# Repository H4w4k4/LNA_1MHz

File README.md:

# LNA_1MHz
10Hz to 1MHz Low Noise Amplifier based on Linear Technology AN-159.

<p align="center">

 &nbsp; &nbsp;

</p>

# Design
The design is based on [Linear Technology AN-159 document](https://www.analog.com/en/resources/app-notes/an-159.html#author). It describe how to build a +80dB 10Hz to 1MHz low noise amplifier in order to measure noise level in the 2nV/√Hz range.

Following changes have been done:
+ Design re-routed in KiCad 7.0 to fit nicely into a Hammond 1590BBS housing
+ Selectable +60dB or +80dB gain
+ Full BW output removed

# Measure
A 60dB attenuator is placed on the input of the LNA to measure the frequency response. An Analog Discovery 3 is used as a network analyser.

# Building it
The complete production files are available. The PCB is a 4-layer 102 x 82.6mm and every components is hand solderable. The LNA is powered by 6x AA batteries, consumption is about 100mA. Use the Gerber "housing_Lid_Drill" for drilling the holes in the housing cover. 

Total BOM cost is ~160USD + PCB + shipping.

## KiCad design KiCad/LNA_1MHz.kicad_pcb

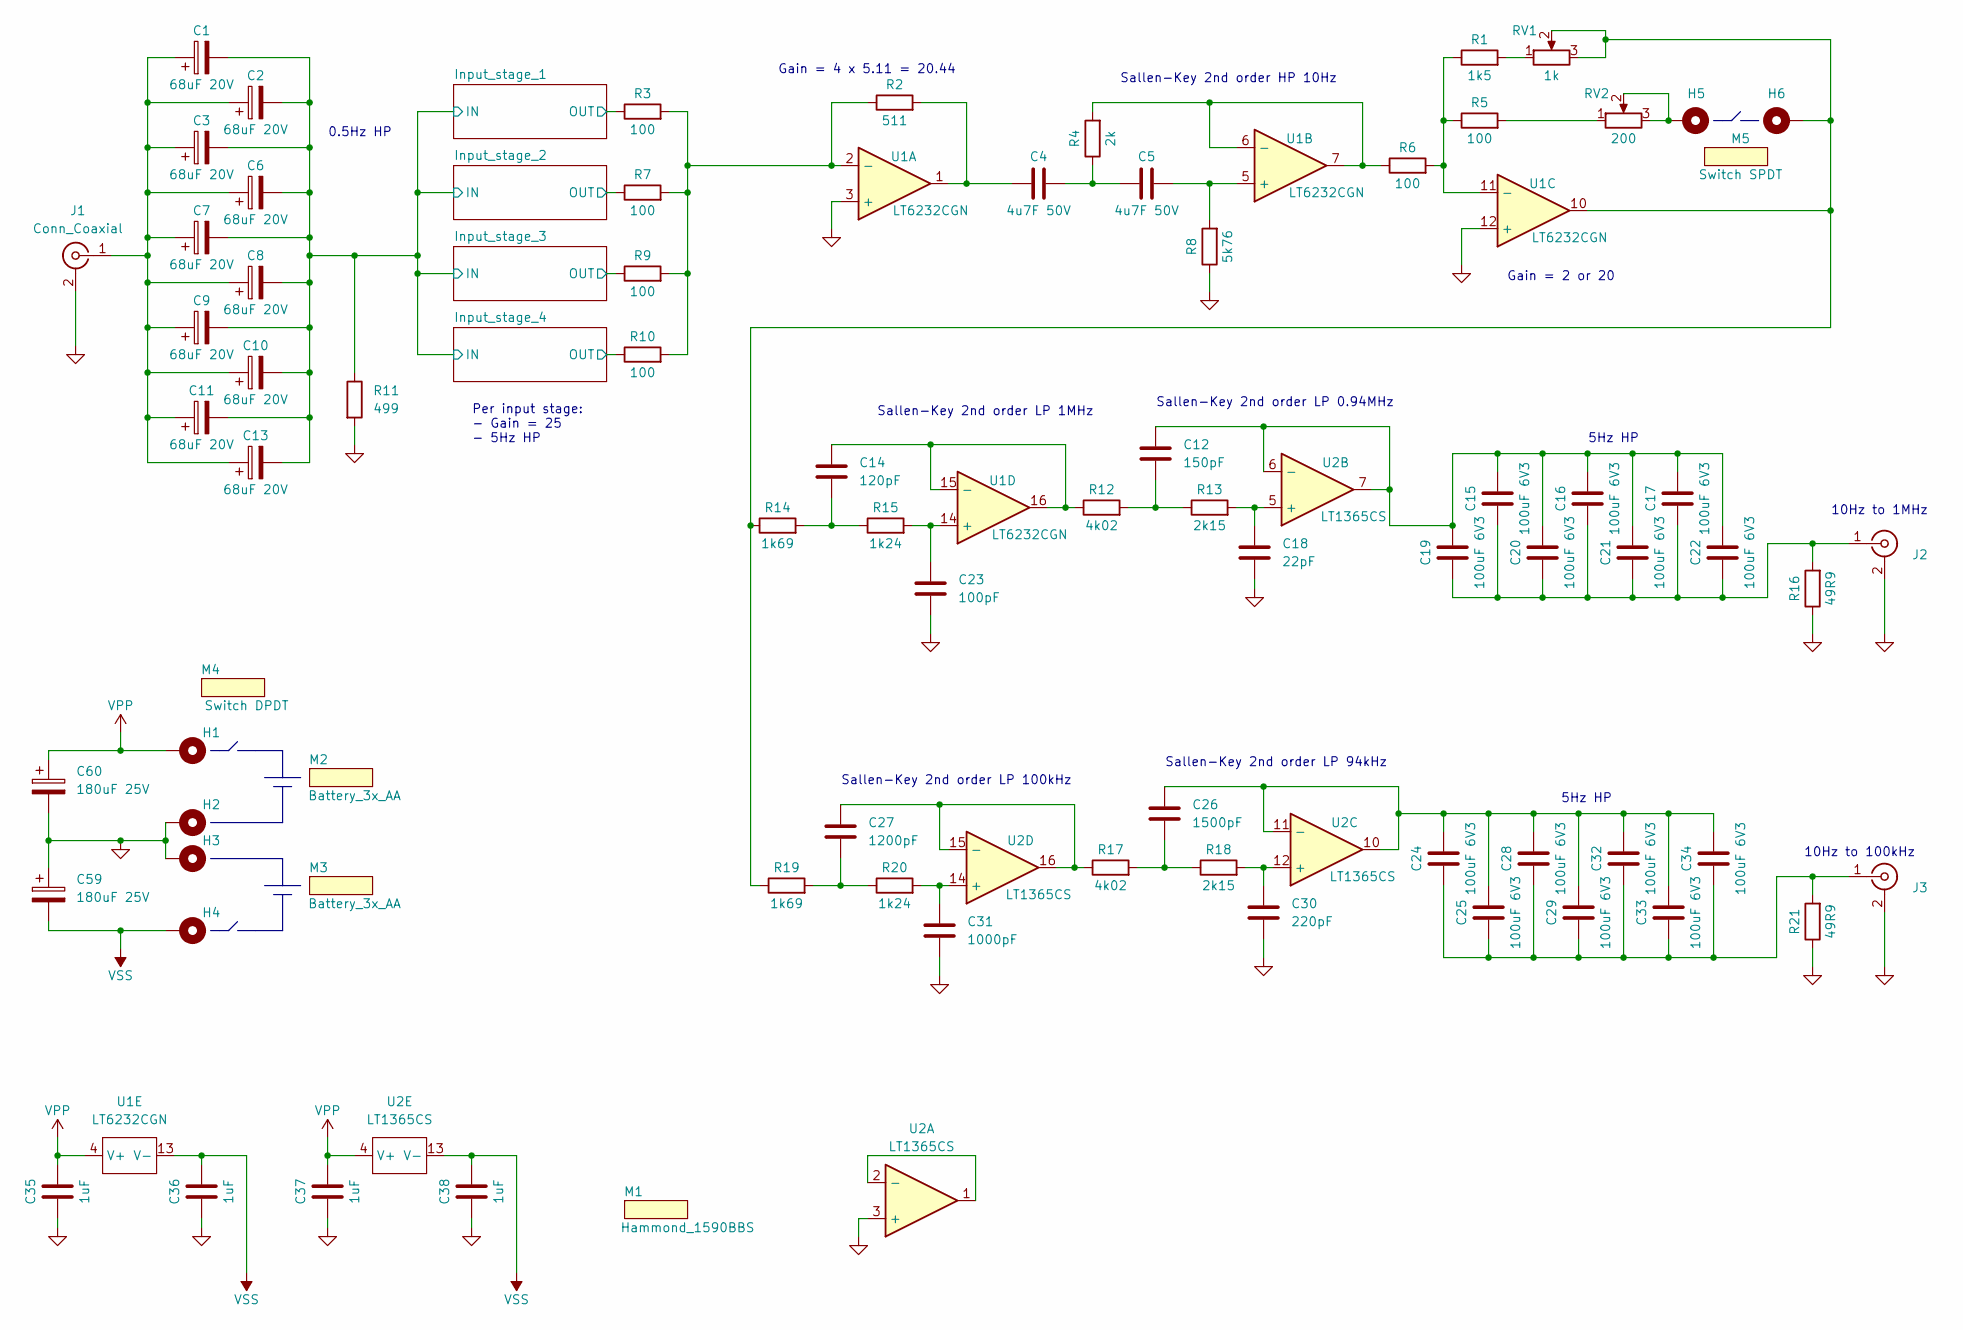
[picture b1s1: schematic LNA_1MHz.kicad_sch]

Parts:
C1, C2, C3, C6, C7, C8, C9, C10, C11, C13: 68uF 20V; CP_EIA-7343-30_AVX-N_Pad2.25x2.55mm_HandSolder; Part AVX, TPSE686M020R0150
C4, C5: 4u7F 50V; C_Rect_L7.2mm_W7.2mm_P5.00mm_FKS2_FKP2_MKS2_MKP2; Part WIMA, MKS2B044701K00K
C12: 150pF; C_1206_3216Metric_Pad1.33x1.80mm_HandSolder; Part AVX, 12065A151JAT2A
C14: 120pF; C_1206_3216Metric_Pad1.33x1.80mm_HandSolder; Part AVX, 12065A121JAT2A
C15, C16, C17, C19, C20, C21, C22, C24, C25, C28, C29, C32, C33, C34: 100uF 6V3; C_1206_3216Metric_Pad1.33x1.80mm_HandSolder; Part MURATA, GRM31CR60J107ME39L
C18: 22pF; C_1206_3216Metric_Pad1.33x1.80mm_HandSolder; Part AVX, 12065A220JAT2A
C23: 100pF; C_1206_3216Metric_Pad1.33x1.80mm_HandSolder; Part AVX, 12065A101JAT2A
C26: 1500pF; C_1206_3216Metric_Pad1.33x1.80mm_HandSolder; Part AVX, 12065A152JAT2A
C27: 1200pF; C_1206_3216Metric_Pad1.33x1.80mm_HandSolder; Part AVX, 12065A122JAT2A
C30: 220pF; C_1206_3216Metric_Pad1.33x1.80mm_HandSolder; Part AVX, 12065A221JAT2A
C31: 1000pF; C_1206_3216Metric_Pad1.33x1.80mm_HandSolder; Part AVX, 12065A102JAT2A
C35, C36, C37, C38: 1uF; C_Rect_L7.2mm_W5.5mm_P5.00mm_FKS2_FKP2_MKS2_MKP2; Part WIMA, MKS2C041001F00K
C59, C60: 180uF 25V; CP_Radial_D8.0mm_P3.50mm; Part PANASONIC, 25SEPF180M
H1, H2, H3, H4, H5, H6: TestPoint_THTPad_2.0x2.0mm_Drill1.0mm
J1: Conn_Coaxial; BNC_TycoElect_5227; Part TE 5227673­1, TE 1­329632­2, TE 1­32963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
J2, J3: Conn_Coaxial; BNC_TycoElect_5227; Part TE 5227222-3, TE 1­329632­2, TE 1­32963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
M1: Hammond_1590BBS; Part Hammond, 1590BBS
M2, M3: Battery_3x_AA; Battery_Holder_3x_AA_no_pin; Part Multicomp, MP000331
M4: Switch DPDT; Multicomp, 1MD1T1B5M1QE; Part Multicomp, 1MD1T1B5M1QE
M5: Switch SPDT; Multicomp, 1MS1T1B5M1QE; Part Multicomp, 1MS1T1B5M1QE
R1: 1k5; R_1206_3216Metric_Pad1.30x1.75mm_HandSolder; Part VISHAY, CRCW12061K50FKEA
R2: 511; R_1206_3216Metric_Pad1.30x1.75mm_HandSolder; Part VISHAY, CRCW1206511RFKEA
R3, R5, R6, R7, R9, R10: 100; R_1206_3216Metric_Pad1.30x1.75mm_HandSolder; Part VISHAY, CRCW1206100RFKEA
R4: 2k; R_1206_3216Metric_Pad1.30x1.75mm_HandSolder; Part VISHAY, CRCW12062K00FKEA
R8: 5k76; R_1206_3216Metric_Pad1.30x1.75mm_HandSolder; Part VISHAY, CRCW12065K76FKEA
R11: 499; R_1206_3216Metric_Pad1.30x1.75mm_HandSolder; Part VISHAY, CRCW1206499RFKEA
R12, R17: 4k02; R_1206_3216Metric_Pad1.30x1.75mm_HandSolder; Part VISHAY, CRCW12064K02FKEA
R13, R18: 2k15; R_1206_3216Metric_Pad1.30x1.75mm_HandSolder; Part VISHAY, CRCW12062K15FKEA
R14, R19: 1k69; R_1206_3216Metric_Pad1.30x1.75mm_HandSolder; Part VISHAY, CRCW12061K69FKEA
R15, R20: 1k24; R_1206_3216Metric_Pad1.30x1.75mm_HandSolder; Part VISHAY, CRCW12061K24FKEA
R16, R21: 49R9; R_1206_3216Metric_Pad1.30x1.75mm_HandSolder; Part VISHAY, CRCW120649R9FKEA
RV1: 1k; Potentiometer_Bourns_3296X_Horizontal; Part BOURNS, 3296X-1-102LF
RV2: 200; Potentiometer_Bourns_3296X_Horizontal; Part BOURNS, 3296X-1-201LF
U1: LT6232CGN; SSOP-16_3.9x4.9mm_P0.635mm; Part Linear Tech., LT6232CGN#PBF
U2: LT1365CS; SO-16_3.9x9.9mm_P1.27mm; Part Linear Tech., LT1365CS#PBF

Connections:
/Input_stage_1/IN: C1.2, C2.2, C3.2, C6.2, C7.2, C8.2, C9.2, C10.2, C11.2, C13.2, R11.1; also elsewhere on the board
/Input_stage_1/OUT: R3.1; also elsewhere on the board
/Input_stage_2/OUT: R7.1; also elsewhere on the board
/Input_stage_3/OUT: R9.1; also elsewhere on the board
/Input_stage_4/OUT: R10.1; also elsewhere on the board
GND: C18.2, C23.2, C30.2, C31.2, C35.1, C36.1, C37.1, C38.1, C59.1, C60.2, H2.1, H3.1, J1.2 (Ext), J2.2 (Ext), J3.2 (Ext), R8.1, R11.2, R16.1, R21.1, U1.3 (+), U1.12 (+), U2.3 (+); also elsewhere on the board
unnamed: C4.1, R2.2, U1.1
unnamed: C4.2, C5.1, R4.1
unnamed: C12.2, R12.2, R13.1
unnamed: C14.2, R14.2, R15.1
unnamed: C26.2, R17.2, R18.1
unnamed: C27.2, R19.2, R20.1
unnamed: H5.1, RV2.2, RV2.3
unnamed: H6.1, R14.1, R19.1, RV1.2, RV1.3, U1.10
unnamed: C1.1, C2.1, C3.1, C6.1, C7.1, C8.1, C9.1, C10.1, C11.1, C13.1, J1.1 (In)
unnamed: C15.1, C16.1, C17.1, C19.1, C20.1, C21.1, C22.1, J2.1 (In), R16.2
unnamed: C24.2, C25.2, C28.2, C29.2, C32.2, C33.2, C34.2, J3.1 (In), R21.2
unnamed: R1.2, RV1.1
unnamed: R5.2, RV2.1
unnamed: R2.1, R3.2, R7.2, R9.2, R10.2, U1.2 (-)
unnamed: C5.2, R8.2, U1.5 (+)
unnamed: R4.2, R6.1, U1.6 (-), U1.7
unnamed: R1.1, R5.1, R6.2, U1.11 (-)
unnamed: C23.1, R15.2, U1.14 (+)
unnamed: C14.1, R12.1, U1.15 (-), U1.16
unnamed: U2.1, U2.2 (-)
unnamed: C18.1, R13.2, U2.5 (+)
unnamed: C12.1, C15.2, C16.2, C17.2, C19.2, C20.2, C21.2, C22.2, U2.6 (-), U2.7
unnamed: C30.1, R18.2, U2.12 (+)
unnamed: C24.1, C25.1, C26.1, C28.1, C29.1, C32.1, C33.1, C34.1, U2.10, U2.11 (-)
unnamed: C31.1, R20.2, U2.14 (+)
unnamed: C27.1, R17.1, U2.15 (-), U2.16
VPP: C35.2, C37.2, C60.1, H1.1, U1.4 (V+), U2.4 (V+); also elsewhere on the board
VSS: C36.2, C38.2, C59.2, H4.1, U1.13 (V-), U2.13 (V-); also elsewhere on the board

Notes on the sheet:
10Hz to 1MHz
Sallen-Key 2nd order LP 1MHz
Sallen-Key 2nd order LP 94kHz
Sallen-Key 2nd order LP 100kHz
Sallen-Key 2nd order HP 10Hz
5Hz HP
0.5Hz HP
Gain = 2 or 20
10Hz to 100kHz
Gain = 4 x 5.11 = 20.44
Per input stage: - Gain = 25 - 5Hz HP
Sallen-Key 2nd order LP 0.94MHz

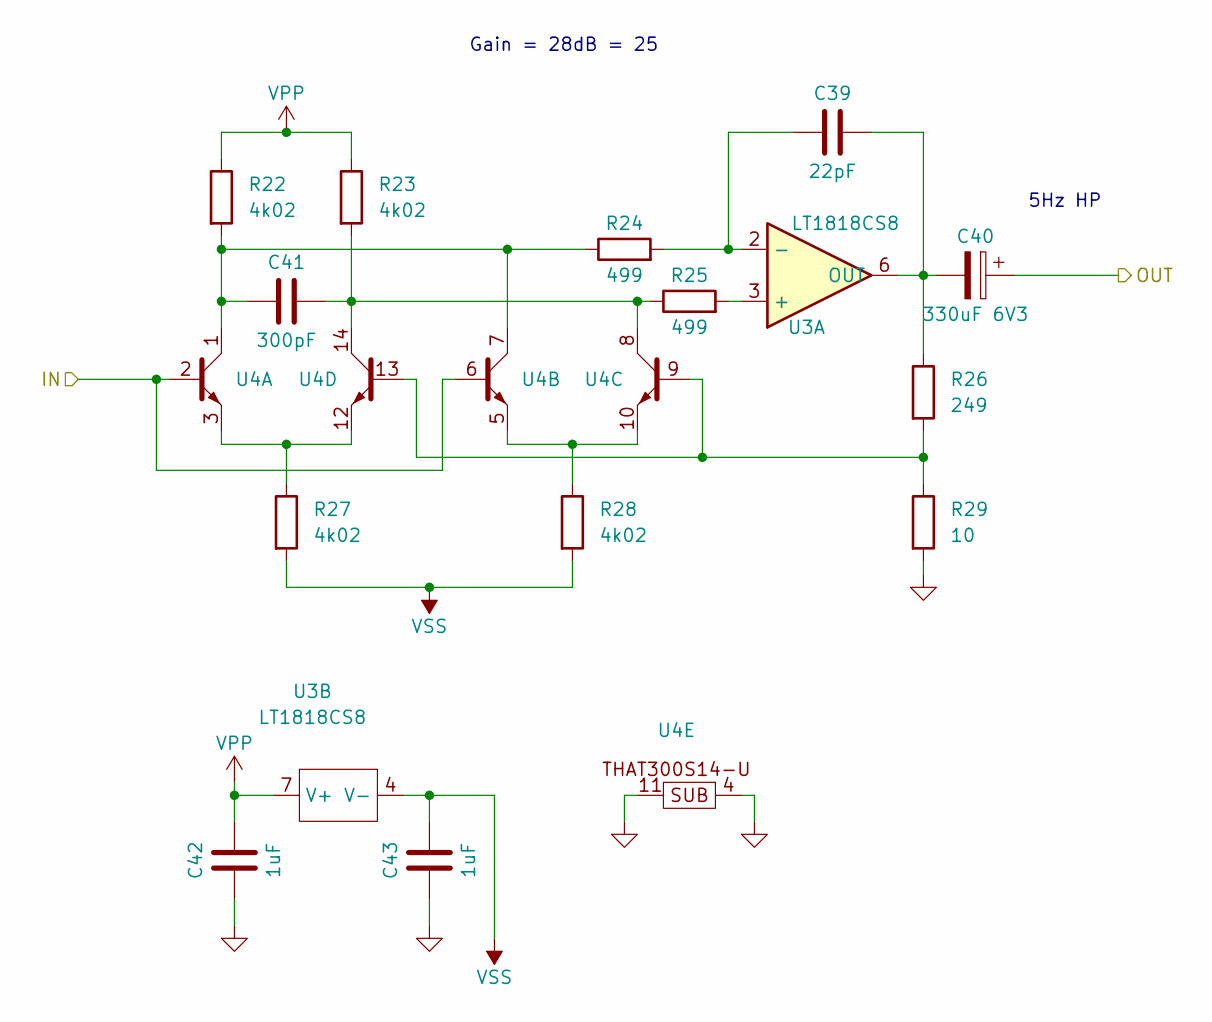
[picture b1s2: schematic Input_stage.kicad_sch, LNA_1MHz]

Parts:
C39: 22pF; C_1206_3216Metric_Pad1.33x1.80mm_HandSolder; Part AVX, 12065A220JAT2A
C40: 330uF 6V3; CP_EIA-7343-30_AVX-N_Pad2.25x2.55mm_HandSolder; Part AVX, TPSD337M006R0100
C41: 300pF; C_0805_2012Metric_Pad1.18x1.45mm_HandSolder; Part AVX, 08053C301JAT2A
C42, C43: 1uF; C_Rect_L7.2mm_W5.5mm_P5.00mm_FKS2_FKP2_MKS2_MKP2; Part WIMA, MKS2C041001F00K
R22, R23, R27, R28: 4k02; R_1206_3216Metric_Pad1.30x1.75mm_HandSolder; Part VISHAY, CRCW12064K02FKEA
R24, R25: 499; R_0805_2012Metric_Pad1.20x1.40mm_HandSolder; Part VISHAY, CRCW0805499RFKEA
R26: 249; R_1206_3216Metric_Pad1.30x1.75mm_HandSolder; Part YAGEO, RC1206FR-07249RL
R29: 10; R_1206_3216Metric_Pad1.30x1.75mm_HandSolder; Part VISHAY, CRCW120610R0FKEAC
U3: LT1818CS8; SO-8_3.9x4.9mm_P1.27mm; Part Linear Tech., LT1818CS8#PBF
U4: THAT300S14-U; SOIC-14_3.9x8.7mm_P1.27mm; Part THAT Corporation, THAT300S14-U

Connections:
/Input_stage_1/IN: U4.2 (B), U4.6 (B); also elsewhere on the board
/Input_stage_1/OUT: C40.1; also elsewhere on the board
GND: C42.1, C43.1, R29.2, U4.4 (SUB), U4.11 (SUB); also elsewhere on the board
unnamed: R25.2, U3.3 (+)
unnamed: C39.1, R24.2, U3.2 (-)
unnamed: C39.2, C40.2, R26.1, U3.6 (OUT)
unnamed: C41.1, R22.2, R24.1, U4.1 (C), U4.7 (C)
unnamed: R27.1, U4.3 (E), U4.12 (E)
unnamed: R28.1, U4.5 (E), U4.10 (E)
unnamed: R26.2, R29.1, U4.9 (B), U4.13 (B)
unnamed: C41.2, R23.2, R25.1, U4.8 (C), U4.14 (C)
VPP: C42.2, R22.1, R23.1, U3.7 (V+); also elsewhere on the board
VSS: C43.2, R27.2, R28.2, U3.4 (V-); also elsewhere on the board

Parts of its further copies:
C44, C49, C54: 22pF; C_1206_3216Metric_Pad1.33x1.80mm_HandSolder; Part AVX, 12065A220JAT2A
C45, C50, C55: 330uF 6V3; CP_EIA-7343-30_AVX-N_Pad2.25x2.55mm_HandSolder; Part AVX, TPSD337M006R0100
C46, C51, C56: 300pF; C_0805_2012Metric_Pad1.18x1.45mm_HandSolder; Part AVX, 08053C301JAT2A
C47, C48, C52, C53, C57, C58: 1uF; C_Rect_L7.2mm_W5.5mm_P5.00mm_FKS2_FKP2_MKS2_MKP2; Part WIMA, MKS2C041001F00K
R30, R31, R35, R36, R38, R39, R43, R44, R46, R47, R51, R52: 4k02; R_1206_3216Metric_Pad1.30x1.75mm_HandSolder; Part VISHAY, CRCW12064K02FKEA
R32, R33, R40, R41, R48, R49: 499; R_0805_2012Metric_Pad1.20x1.40mm_HandSolder; Part VISHAY, CRCW0805499RFKEA
R34, R42, R50: 249; R_1206_3216Metric_Pad1.30x1.75mm_HandSolder; Part YAGEO, RC1206FR-07249RL
R37, R45, R53: 10; R_1206_3216Metric_Pad1.30x1.75mm_HandSolder; Part VISHAY, CRCW120610R0FKEAC
U5, U7, U9: LT1818CS8; SO-8_3.9x4.9mm_P1.27mm; Part Linear Tech., LT1818CS8#PBF
U6, U8, U10: THAT300S14-U; SOIC-14_3.9x8.7mm_P1.27mm; Part THAT Corporation, THAT300S14-U

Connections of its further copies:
/Input_stage_1/IN: U6.2 (B), U6.6 (B), U8.2 (B), U8.6 (B), U10.2 (B), U10.6 (B); also elsewhere on the board
/Input_stage_2/OUT: C45.1; also elsewhere on the board
/Input_stage_3/OUT: C50.1; also elsewhere on the board
/Input_stage_4/OUT: C55.1; also elsewhere on the board
GND: C47.1, C48.1, C52.1, C53.1, C57.1, C58.1, R37.2, R45.2, R53.2, U6.4 (SUB), U6.11 (SUB), U8.4 (SUB), U8.11 (SUB), U10.4 (SUB), U10.11 (SUB); also elsewhere on the board
unnamed: R33.2, U5.3 (+)
unnamed: C44.1, R32.2, U5.2 (-)
unnamed: C44.2, C45.2, R34.1, U5.6 (OUT)
unnamed: C46.1, R30.2, R32.1, U6.1 (C), U6.7 (C)
unnamed: R35.1, U6.3 (E), U6.12 (E)
unnamed: R36.1, U6.5 (E), U6.10 (E)
unnamed: R34.2, R37.1, U6.9 (B), U6.13 (B)
unnamed: C46.2, R31.2, R33.1, U6.8 (C), U6.14 (C)
unnamed: R41.2, U7.3 (+)
unnamed: C49.1, R40.2, U7.2 (-)
unnamed: C49.2, C50.2, R42.1, U7.6 (OUT)
unnamed: C51.1, R38.2, R40.1, U8.1 (C), U8.7 (C)
unnamed: R43.1, U8.3 (E), U8.12 (E)
unnamed: R44.1, U8.5 (E), U8.10 (E)
unnamed: R42.2, R45.1, U8.9 (B), U8.13 (B)
unnamed: C51.2, R39.2, R41.1, U8.8 (C), U8.14 (C)
unnamed: R49.2, U9.3 (+)
unnamed: C54.1, R48.2, U9.2 (-)
unnamed: C54.2, C55.2, R50.1, U9.6 (OUT)
unnamed: C56.1, R46.2, R48.1, U10.1 (C), U10.7 (C)
unnamed: R51.1, U10.3 (E), U10.12 (E)
unnamed: R52.1, U10.5 (E), U10.10 (E)
unnamed: R50.2, R53.1, U10.9 (B), U10.13 (B)
unnamed: C56.2, R47.2, R49.1, U10.8 (C), U10.14 (C)
VPP: C47.2, C52.2, C57.2, R30.1, R31.1, R38.1, R39.1, R46.1, R47.1, U5.7 (V+), U7.7 (V+), U9.7 (V+); also elsewhere on the board
VSS: C48.2, C53.2, C58.2, R35.2, R36.2, R43.2, R44.2, R51.2, R52.2, U5.4 (V-), U7.4 (V-), U9.4 (V-); also elsewhere on the board

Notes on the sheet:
5Hz HP
Gain = 28dB = 25

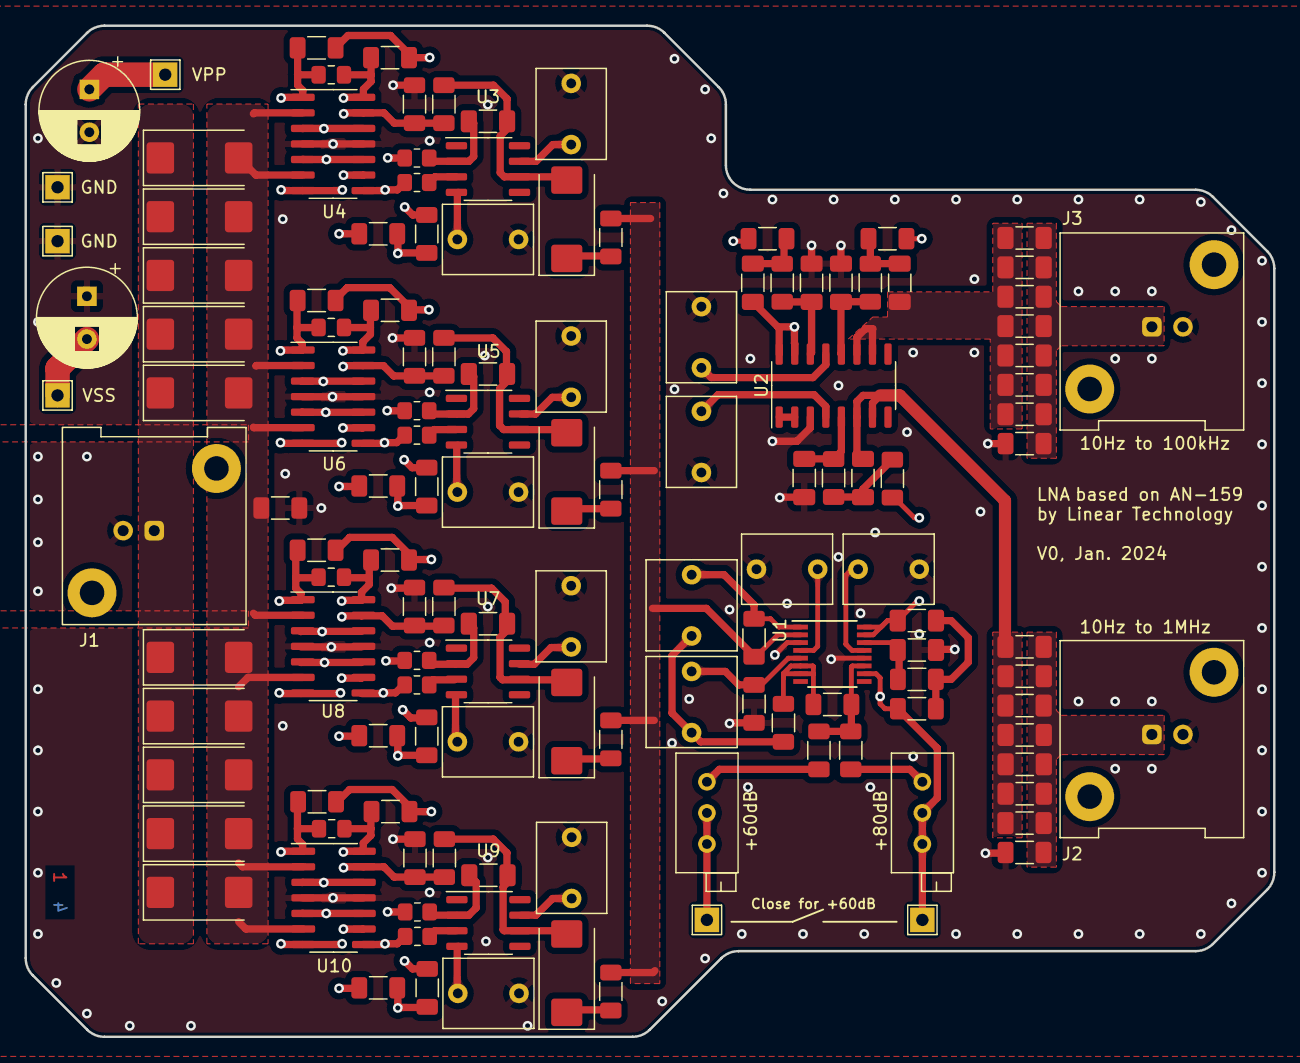
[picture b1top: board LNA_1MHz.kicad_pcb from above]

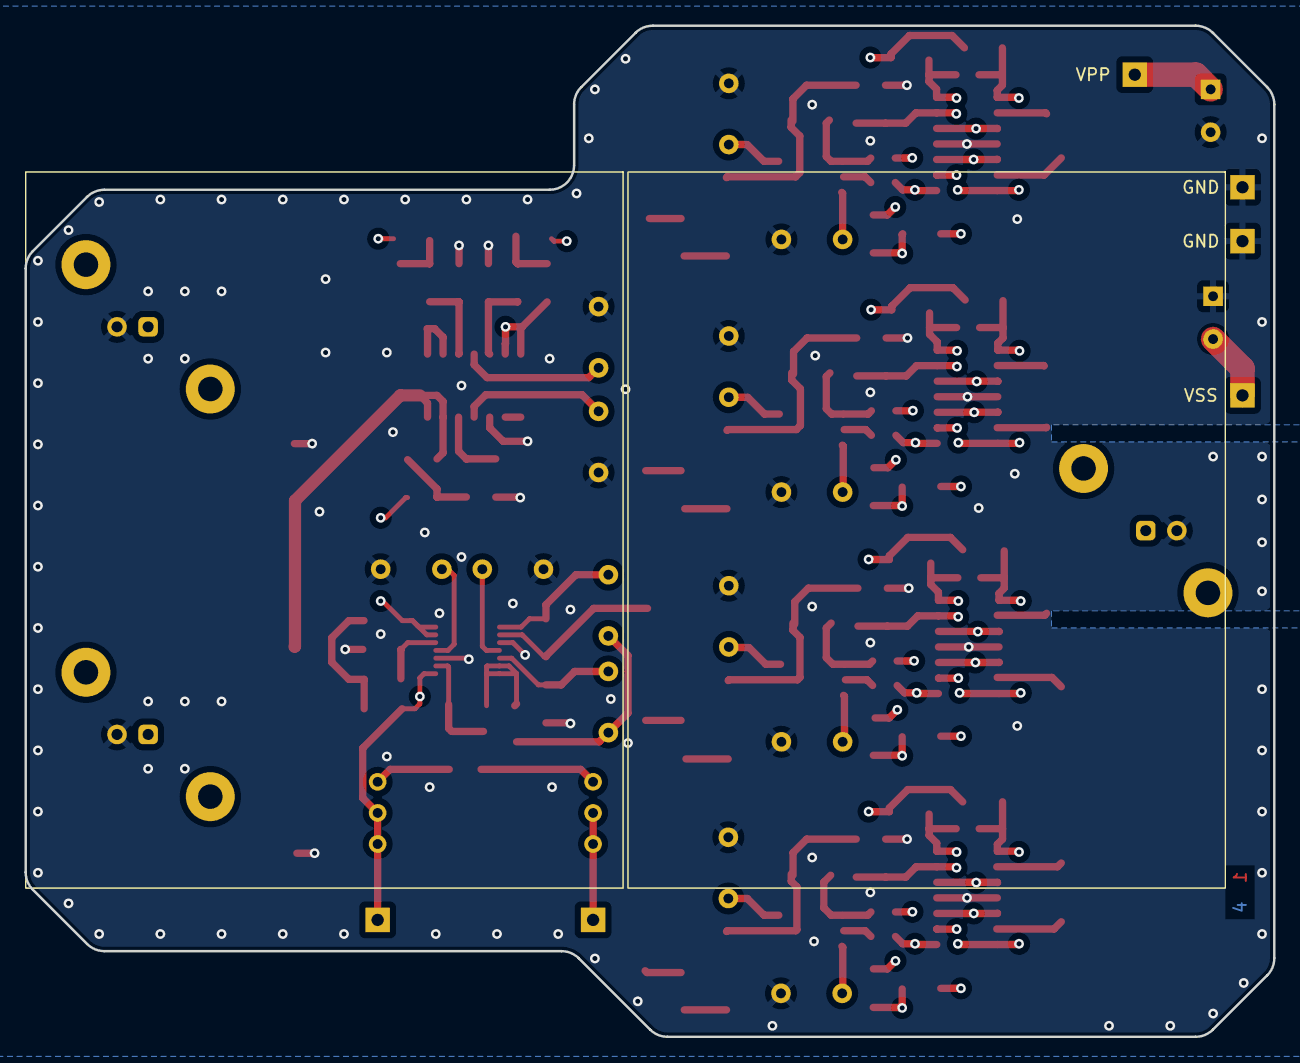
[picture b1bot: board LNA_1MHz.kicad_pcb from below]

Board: 4 copper layers, 102.0 x 82.6 mm, 139 parts (2 on the bottom side), 66 nets.

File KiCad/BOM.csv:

"Reference","Value","Footprint","Datasheet","Part","Qté"
"C1-C3, C6-C11, C13","68uF 20V","Capacitor_Tantalum_SMD:CP_EIA-7343-30_AVX-N_Pad2.25x2.55mm_HandSolder","~","AVX, TPSE686M020R0150","10"
"C4, C5","4u7F 50V","Capacitor_THT:C_Rect_L7.2mm_W7.2mm_P5.00mm_FKS2_FKP2_MKS2_MKP2","~","WIMA, MKS2B044701K00K","2"
"C12","150pF","Capacitor_SMD:C_1206_3216Metric_Pad1.33x1.80mm_HandSolder","~","AVX, 12065A151JAT2A","1"
"C14","120pF","Capacitor_SMD:C_1206_3216Metric_Pad1.33x1.80mm_HandSolder","~","AVX, 12065A121JAT2A","1"
"C15-C17, C19-C22, C24, C25, C28, C29, C32-C34","100uF 6V3","Capacitor_SMD:C_1206_3216Metric_Pad1.33x1.80mm_HandSolder","~","MURATA, GRM31CR60J107ME39L","14"
"C18, C39, C44, C49, C54","22pF","Capacitor_SMD:C_1206_3216Metric_Pad1.33x1.80mm_HandSolder","~","AVX, 12065A220JAT2A","5"
"C23","100pF","Capacitor_SMD:C_1206_3216Metric_Pad1.33x1.80mm_HandSolder","~","AVX, 12065A101JAT2A","1"
"C26","1500pF","Capacitor_SMD:C_1206_3216Metric_Pad1.33x1.80mm_HandSolder","~","AVX, 12065A152JAT2A","1"
"C27","1200pF","Capacitor_SMD:C_1206_3216Metric_Pad1.33x1.80mm_HandSolder","~","AVX, 12065A122JAT2A","1"
"C30","220pF","Capacitor_SMD:C_1206_3216Metric_Pad1.33x1.80mm_HandSolder","~","AVX, 12065A221JAT2A","1"
"C31","1000pF","Capacitor_SMD:C_1206_3216Metric_Pad1.33x1.80mm_HandSolder","~","AVX, 12065A102JAT2A","1"
"C35-C38, C42, C43, C47, C48, C52, C53, C57, C58","1uF","Capacitor_THT:C_Rect_L7.2mm_W5.5mm_P5.00mm_FKS2_FKP2_MKS2_MKP2","~","WIMA, MKS2C041001F00K","12"
"C40, C45, C50, C55","330uF 6V3","Capacitor_Tantalum_SMD:CP_EIA-7343-30_AVX-N_Pad2.25x2.55mm_HandSolder","~","AVX, TPSD337M006R0100","4"
"C41, C46, C51, C56","300pF","Capacitor_SMD:C_0805_2012Metric_Pad1.18x1.45mm_HandSolder","~","AVX, 08053C301JAT2A","4"
"C59, C60","180uF 25V","Capacitor_THT:CP_Radial_D8.0mm_P3.50mm","~","PANASONIC, 25SEPF180M","2"
"H1-H6","~","TestPoint:TestPoint_THTPad_2.0x2.0mm_Drill1.0mm","~","","6"
"J1-J3","Conn_Coaxial","User_footprint:BNC_TycoElect_5227"," ~","-- valeurs mixtées --","3"
"M1","Hammond_1590BBS","User_footprint:Hammond_1590BBS","","Hammond, 1590BBS","1"
"M2, M3","Battery_3x_AA","User_footprint:Battery_Holder_3x_AA_no_pin","","Multicomp, MP000331","2"
"M4","Switch DPDT","User_footprint:Multicomp, 1MD1T1B5M1QE","","Multicomp, 1MD1T1B5M1QE","1"
"M5","Switch SPDT","User_footprint:Multicomp, 1MS1T1B5M1QE","","Multicomp, 1MS1T1B5M1QE","1"
"R1","1k5","Resistor_SMD:R_1206_3216Metric_Pad1.30x1.75mm_HandSolder","~","VISHAY, CRCW12061K50FKEA","1"
"R2","511","Resistor_SMD:R_1206_3216Metric_Pad1.30x1.75mm_HandSolder","~","VISHAY, CRCW1206511RFKEA","1"
"R3, R5-R7, R9, R10","100","Resistor_SMD:R_1206_3216Metric_Pad1.30x1.75mm_HandSolder","~","VISHAY, CRCW1206100RFKEA","6"
"R4","2k","Resistor_SMD:R_1206_3216Metric_Pad1.30x1.75mm_HandSolder","~","VISHAY, CRCW12062K00FKEA","1"
"R8","5k76","Resistor_SMD:R_1206_3216Metric_Pad1.30x1.75mm_HandSolder","~","VISHAY, CRCW12065K76FKEA","1"
"R11","499","Resistor_SMD:R_1206_3216Metric_Pad1.30x1.75mm_HandSolder","~","VISHAY, CRCW1206499RFKEA","1"
"R12, R17, R22, R23, R27, R28, R30, R31, R35, R36, R38, R39, R43, R44, R46, R47, R51, R52","4k02","Resistor_SMD:R_1206_3216Metric_Pad1.30x1.75mm_HandSolder","~","VISHAY, CRCW12064K02FKEA","18"
"R13, R18","2k15","Resistor_SMD:R_1206_3216Metric_Pad1.30x1.75mm_HandSolder","~","VISHAY, CRCW12062K15FKEA","2"
"R14, R19","1k69","Resistor_SMD:R_1206_3216Metric_Pad1.30x1.75mm_HandSolder","~","VISHAY, CRCW12061K69FKEA","2"
"R15, R20","1k24","Resistor_SMD:R_1206_3216Metric_Pad1.30x1.75mm_HandSolder","~","VISHAY, CRCW12061K24FKEA","2"
"R16, R21","49R9","Resistor_SMD:R_1206_3216Metric_Pad1.30x1.75mm_HandSolder","~","VISHAY, CRCW120649R9FKEA","2"
"R24, R25, R32, R33, R40, R41, R48, R49","499","Resistor_SMD:R_0805_2012Metric_Pad1.20x1.40mm_HandSolder","~","VISHAY, CRCW0805499RFKEA","8"
"R26, R34, R42, R50","249","Resistor_SMD:R_1206_3216Metric_Pad1.30x1.75mm_HandSolder","~","YAGEO, RC1206FR-07249RL","4"
"R29, R37, R45, R53","10","Resistor_SMD:R_1206_3216Metric_Pad1.30x1.75mm_HandSolder","~","VISHAY, CRCW120610R0FKEAC","4"
"RV1","1k","Potentiometer_THT:Potentiometer_Bourns_3296X_Horizontal","~","BOURNS, 3296X-1-102LF","1"
"RV2","200","Potentiometer_THT:Potentiometer_Bourns_3296X_Horizontal","~","BOURNS, 3296X-1-201LF","1"
"U1","LT6232CGN","Package_SO:SSOP-16_3.9x4.9mm_P0.635mm","https://www.analog.com/media/en/technical-documentation/data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","Linear Tech., LT6232CGN#PBF","1"
"U2","LT1365CS","Package_SO:SO-16_3.9x9.9mm_P1.27mm","https://www.analog.com/media/en/technical-documentation/data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","Linear Tech., LT1365CS#PBF","1"
"U3, U5, U7, U9","LT1818CS8","Package_SO:SO-8_3.9x4.9mm_P1.27mm","https://www.analog.com/media/en/technical-documentation/data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","Linear Tech., LT1818CS8#PBF","4"
"U4, U6, U8, U10","THAT300S14-U","Package_SO:SOIC-14_3.9x8.7mm_P1.27mm","","THAT Corporation, THAT300S14-U","4"

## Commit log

2024-02-09 Graph now shows the true LNA gain
